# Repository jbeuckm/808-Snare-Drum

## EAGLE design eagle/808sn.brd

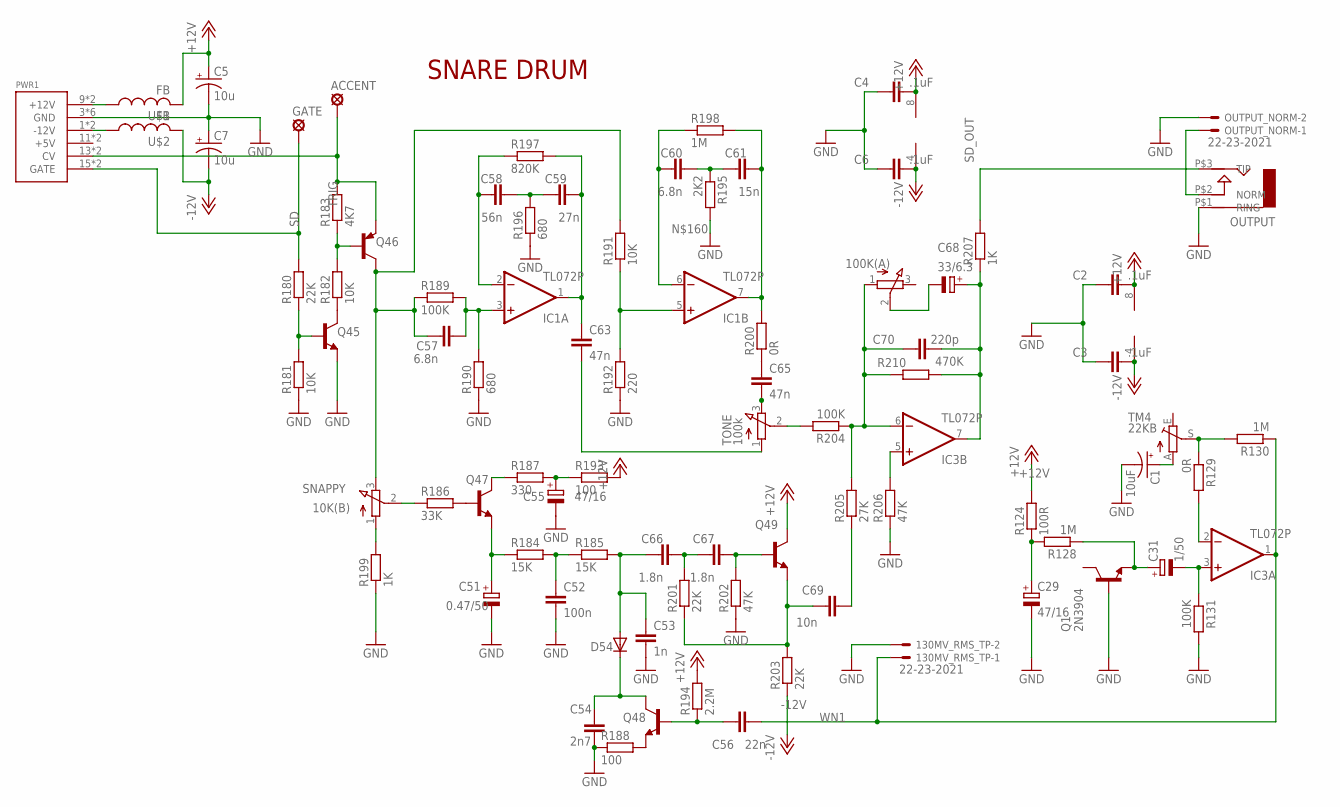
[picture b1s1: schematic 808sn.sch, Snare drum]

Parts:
130MV_RMS_TP: 22-23-2021
ACCENT: LSP10
C1: 10uF; B45181A
C2, C3, C4: .1uF; C025-025X050
C5, C7: 10u; B45181A
C6: .1uF; C050-025X075
C29: 47/16; E2,5-5
C31: 1/50; E3,5-8
C51: 0.47/50; E3,5-8
C52: 100n; C050-045X075
C53: 1n; C035-025X75
C54: 2n7; C035-025X75
C55: 47/16; E2-5
C56: 22n; C035-030X60
C57, C60: 6.8n; C035-030X60
C58: 56n; C050-024X044
C59: 27n; C050-024X044
C61: 15n; C035-030X60
C63, C65: 47n; C050-024X044
C66, C67: 1.8n; C035-025X75
C68: 33/6.3; E2-5
C69: 10n; C075-042X103
C70: 220p; C025-025X050
D54: 1N4148DO35-7; DO35-7
GATE: LSP10
IC1, IC3: TL072P; DIL08
LEVEL: 100K(A); 3RP/1610N
OUTPUT: AUDIO-JACK; ERTHENVAR-JACK-90DEG
OUTPUT_NORM: 22-23-2021
PWR1: POWER; POWER_16
Q1, Q45, Q47, Q48, Q49: 2N3904; TO92
Q46: 2N3906; TO92
R124: 100R; 0207/7
R128, R130: 1M; 0207/7
R129: 0R; 0207/7
R131, R204: 100K; 0207/7
R180: 22K; 0207/5V
R181, R182, R191: 10K; 0207/5V
R183: 4K7; 0207/2V
R184, R185: 15K; 0207/7
R186: 33K; 0309/12
R187: 330; 0207/7
R188: 100; 0207/5V
R189: 100K; 0207/5V
R190: 680; 0207/5V
R192: 220; 0207/5V
R193: 100; 0207/7
R194: 2.2M; 0207/7
R195: 2K2; 0207/7
R196: 680; 0207/7
R197: 820K; 0207/5V
R198: 1M; 0207/5V
R199: 1K; 0207/5V
R200: 0R; 0207/5V
R201, R203: 22K; 0207/7
R202, R206: 47K; 0207/5V
R205: 27K; 0207/7
R207: 1K; 0309/10
R210: 470K; 0207/5V
SNAPPY: 10K(B); 3RP/1610N
TM4: 22KB; B64Y
TONE: 100k; 3RP/1610N
U$1, U$2: FB

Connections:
+12V: C2.2, C4.2, C5.+, IC1.8 (V+), IC3.8 (V+), Q49.1 (C), R124.2, R193.2, R194.2, U$1.P$2 (2)
-12V: C3.2, C6.2, C7.-, IC1.4 (V-), IC3.4 (V-), R203.1, U$2.P$2 (2)
GND: 130MV_RMS_TP.2, C1.-, C2.1, C3.1, C4.1, C5.-, C6.1, C7.+, C29.-, C51.-, C52.2, C53.P$2 (2), C54.P$2 (2), C55.-, OUTPUT.P$1 (RING), OUTPUT_NORM.2, PWR1.3 (GND), PWR1.4 (GND), PWR1.5 (GND), PWR1.6 (GND), PWR1.7 (GND), PWR1.8 (GND), Q1.2 (B), Q45.3 (E), R131.2, R181.1, R188.1, R190.1, R192.1, R195.2, R196.1, R199.1, R202.1, R206.1
unnamed: IC3.5 (+IN), R206.2
unnamed: OUTPUT.P$2 (NORM), OUTPUT_NORM.1
unnamed: C1.+, TM4.A
unnamed: IC3.2 (-IN), R129.2
unnamed: Q45.2 (B), R180.1, R181.2
unnamed: Q46.2 (B), R182.2, R183.1
unnamed: Q45.1 (C), R182.1
unnamed: C57.P$2 (2), IC1.3 (+IN), R189.2, R190.2
unnamed: C57.P$1 (1), Q46.1 (C), R189.1, R191.2, SNAPPY.3 (E)
unnamed: PWR1.9 (+12V), PWR1.10 (+12V), U$1.P$1 (1)
unnamed: C58.1, IC1.2 (-IN), R197.1
unnamed: C59.2, C63.1, IC1.1 (OUT), R197.2
unnamed: C58.2, C59.1, R196.2
unnamed: C61.P$2 (2), IC1.7 (OUT), R198.2, R200.2
unnamed: C60.P$2 (2), C61.P$1 (1), R195.1
unnamed: IC1.5 (+IN), R191.1, R192.2
unnamed: C63.2, TONE.1 (A)
unnamed: C65.2, TONE.3 (E)
unnamed: C65.1, R200.1
unnamed: R199.2, SNAPPY.1 (A)
unnamed: C52.1, R184.2, R185.1
unnamed: R186.1, SNAPPY.2 (S)
unnamed: Q47.2 (B), R186.2
unnamed: Q47.1 (C), R187.1
unnamed: C55.+, R187.2, R193.1
unnamed: C51.+, Q47.3 (E), R184.1
unnamed: C53.P$1 (1), C66.P$1 (1), D54.A, R185.2
unnamed: C66.P$2 (2), C67.P$1 (1), R201.2
unnamed: C67.P$2 (2), Q49.2 (B), R202.2
unnamed: C69.1, Q49.3 (E), R201.1, R203.2
unnamed: Q48.3 (E), R188.2
unnamed: C54.P$1 (1), D54.C, Q48.1 (C)
unnamed: C56.P$1 (1), Q48.2 (B), R194.1
unnamed: R204.2, TONE.2 (S)
unnamed: C70.1, IC3.6 (-IN), LEVEL.1 (A), R204.1, R205.2, R210.1
unnamed: C69.2, R205.1
unnamed: PWR1.1 (-12V), PWR1.2 (-12V), U$2.P$1 (1)
unnamed: C68.+, C70.2, IC3.7 (OUT), R207.1, R210.2
unnamed: C68.-, LEVEL.2 (S)
unnamed: C60.P$1 (1), IC1.6 (-IN), R198.1
unnamed: C31.-, IC3.3 (+IN), R131.1
unnamed: R129.1, R130.2, TM4.S
unnamed: C31.+, Q1.3 (E), R128.1
unnamed: C29.+, R124.1, R128.2
SD: GATE.MP, PWR1.15 (GATE), PWR1.16 (GATE), R180.2
SD_OUT: OUTPUT.P$3 (TIP), R207.2
TRIG: ACCENT.MP, PWR1.13 (CV), PWR1.14 (CV), Q46.3 (E), R183.2
WN1: 130MV_RMS_TP.1, C56.P$2 (2), IC3.1 (OUT), R130.1

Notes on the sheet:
SNARE DRUM

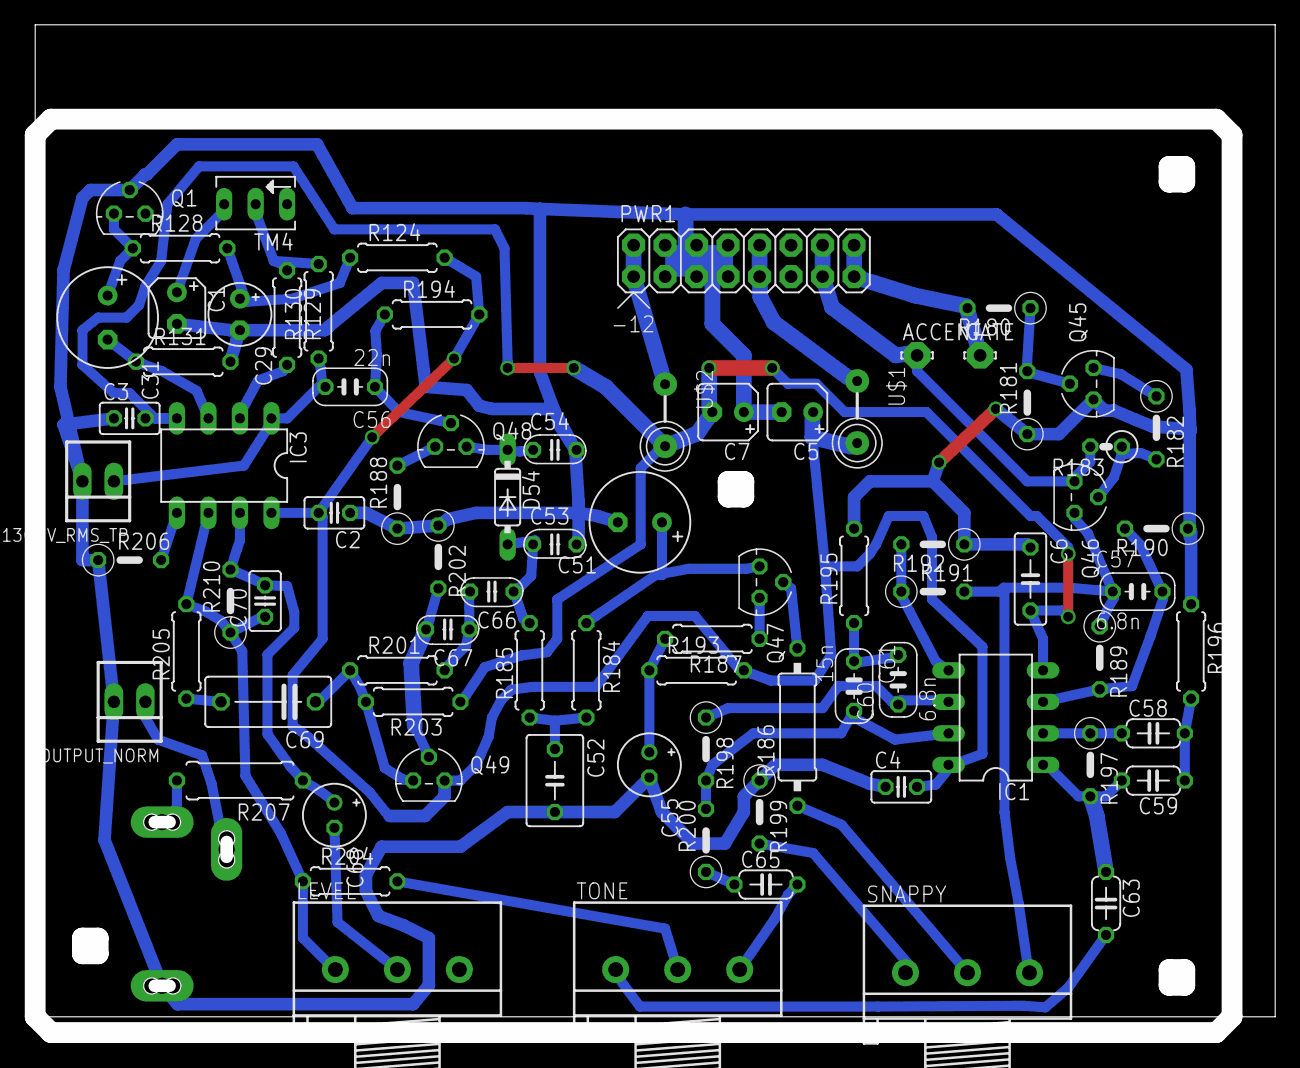
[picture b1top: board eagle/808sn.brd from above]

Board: 2 copper layers, 99.2 x 80.4 mm, 82 parts (0 on the bottom side), 51 nets.

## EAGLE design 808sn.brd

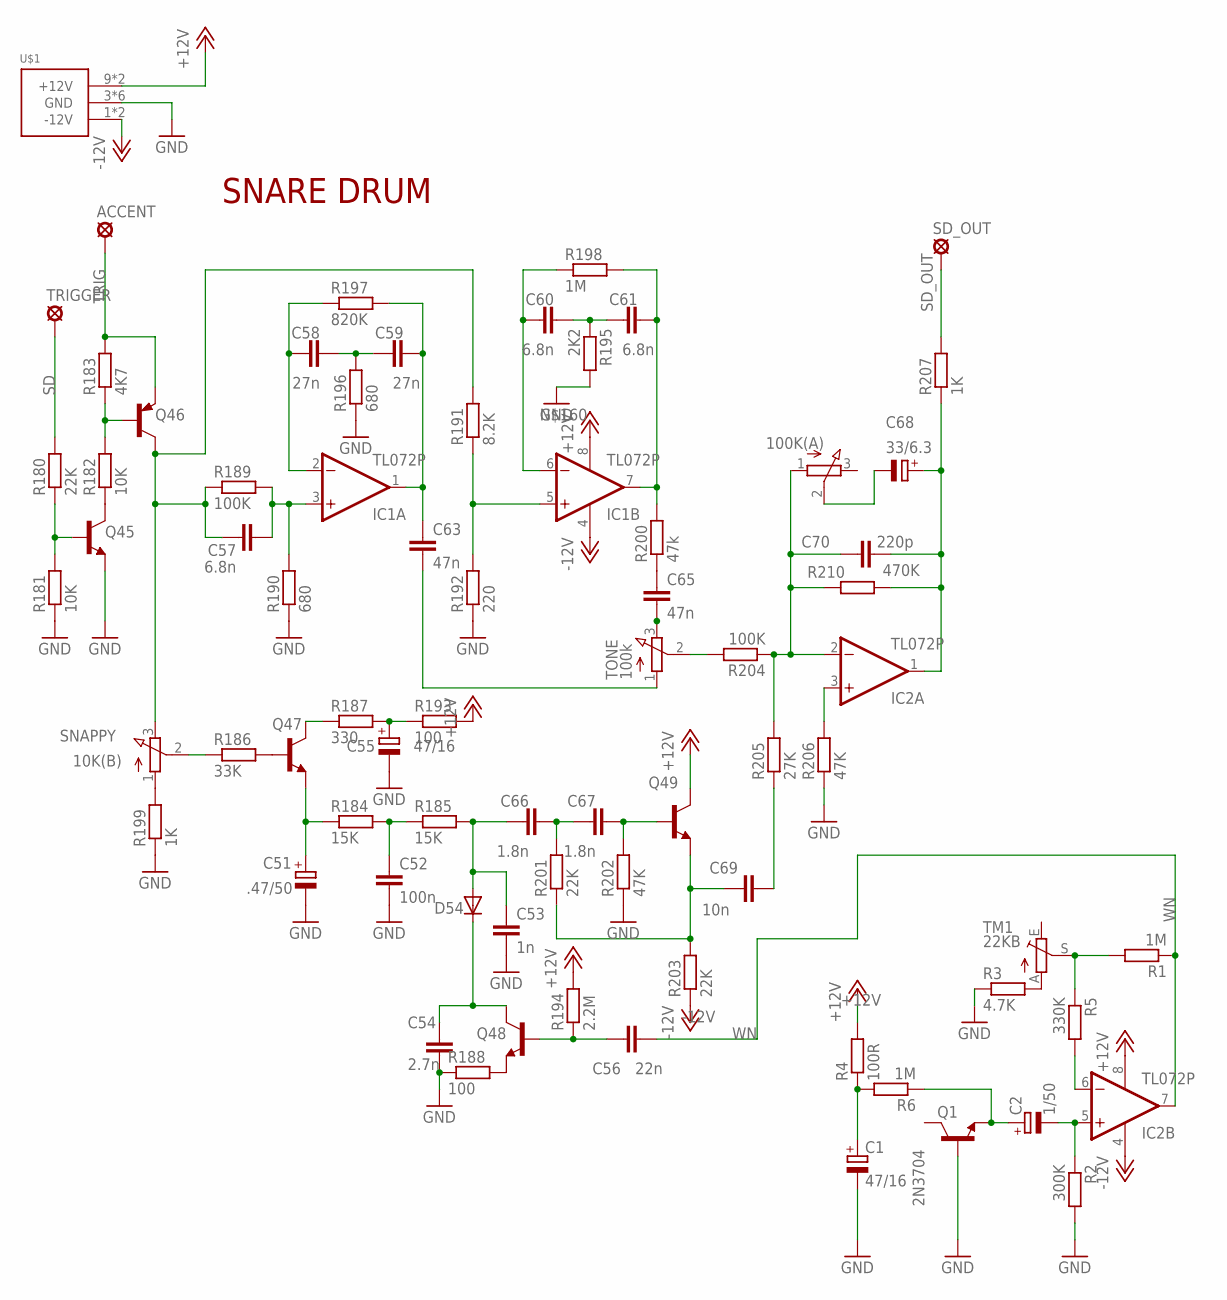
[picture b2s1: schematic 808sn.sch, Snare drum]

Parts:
ACCENT: LSP11
C1: 47/16; E2,5-5
C2: 1/50; E2,5-5
C51: .47/50; E2-5
C52: 100n; C075-032X103
C53: 1n; C035-025X75
C54: 2.7n; C035-025X75
C55: 47/16; E2-5
C56: 22n; C035-030X60
C57, C60, C61: 6.8n; C035-030X60
C58, C59: 27n; C050-024X044
C63, C65: 47n; C050-024X044
C66, C67: 1.8n; C035-025X75
C68: 33/6.3; E2-5
C69: 10n; C035-025X75
C70: 220p; C025-025X050
D54: 1N4148DO35-7; DO35-7
IC1, IC2: TL072P; DIL08
LEVEL: 100K(A); 3RP/1610N
Q1: 2N3704; TO92
Q45, Q47, Q48, Q49: BC546A; TO92-EBC
Q46: BC556; TO92-EBC
R1, R6, R198: 1M; 0207/5V
R2: 300K; 0207/5V
R3: 4.7K; 0207/5V
R4: 100R; 0207/5V
R5: 330K; 0207/5V
R180, R201, R203: 22K; 0207/5V
R181, R182: 10K; 0207/5V
R183: 4K7; 0207/5V
R184, R185: 15K; 0207/5V
R186: 33K; 0207/5V
R187: 330; 0207/5V
R188, R193: 100; 0207/5V
R189, R204: 100K; 0207/5V
R190, R196: 680; 0207/5V
R191: 8.2K; 0207/5V
R192: 220; 0207/5V
R194: 2.2M; 0207/5V
R195: 2K2; 0207/5V
R197: 820K; 0207/5V
R199, R207: 1K; 0207/5V
R200: 47k; 0207/5V
R202, R206: 47K; 0207/5V
R205: 27K; 0207/5V
R210: 470K; 0207/5V
SD_OUT: LSP11
SNAPPY: 10K(B); 3RP/1610N
TM1: 22KB; S64YW
TONE: 100k; 3RP/1610N
TRIGGER: LSP11
U$1: POWER_SIMPLE10; POWER_10

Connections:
+12V: IC1.8 (V+), IC2.8 (V+), Q49.C, R4.2, R193.2, R194.2, U$1.9 (+12V), U$1.10 (+12V)
-12V: IC1.4 (V-), IC2.4 (V-), R203.1, U$1.1 (-12V), U$1.2 (-12V)
GND: C1.-, C51.-, C52.2, C53.P$2 (2), C54.P$2 (2), C55.-, Q1.1 (B), Q45.E, R2.2, R3.1, R181.1, R188.1, R190.1, R192.1, R195.2, R196.1, R199.1, R202.1, R206.1, U$1.3 (GND), U$1.4 (GND), U$1.5 (GND), U$1.6 (GND), U$1.7 (GND), U$1.8 (GND)
unnamed: IC2.3 (+IN), R206.2
unnamed: C2.-, IC2.5 (+IN), R2.1
unnamed: IC2.6 (-IN), R5.2
unnamed: Q45.B, R180.1, R181.2
unnamed: Q46.B, R182.2, R183.1
unnamed: Q45.C, R182.1
unnamed: C57.P$2 (2), IC1.3 (+IN), R189.2, R190.2
unnamed: C57.P$1 (1), Q46.C, R189.1, R191.2, SNAPPY.3 (E)
unnamed: C58.1, IC1.2 (-IN), R197.1
unnamed: C59.2, C63.1, IC1.1 (OUT), R197.2
unnamed: C58.2, C59.1, R196.2
unnamed: C61.P$2 (2), IC1.7 (OUT), R198.2, R200.2
unnamed: C60.P$2 (2), C61.P$1 (1), R195.1
unnamed: IC1.5 (+IN), R191.1, R192.2
unnamed: C63.2, TONE.1 (A)
unnamed: C65.2, TONE.3 (E)
unnamed: C65.1, R200.1
unnamed: R199.2, SNAPPY.1 (A)
unnamed: C52.1, R184.2, R185.1
unnamed: R186.1, SNAPPY.2 (S)
unnamed: Q47.B, R186.2
unnamed: Q47.C, R187.1
unnamed: C55.+, R187.2, R193.1
unnamed: C51.+, Q47.E, R184.1
unnamed: C53.P$1 (1), C66.P$1 (1), D54.A, R185.2
unnamed: C66.P$2 (2), C67.P$1 (1), R201.2
unnamed: C67.P$2 (2), Q49.B, R202.2
unnamed: C69.P$1 (1), Q49.E, R201.1, R203.2
unnamed: Q48.E, R188.2
unnamed: C54.P$1 (1), D54.C, Q48.C
unnamed: C56.P$1 (1), Q48.B, R194.1
unnamed: R204.2, TONE.2 (S)
unnamed: C70.1, IC2.2 (-IN), LEVEL.1 (A), R204.1, R205.2, R210.1
unnamed: C69.P$2 (2), R205.1
unnamed: C68.+, C70.2, IC2.1 (OUT), R207.1, R210.2
unnamed: C68.-, LEVEL.2 (S)
unnamed: C60.P$1 (1), IC1.6 (-IN), R198.1
unnamed: R1.2, R5.1, TM1.S
unnamed: C2.+, Q1.3 (E), R6.1
unnamed: C1.+, R4.1, R6.2
unnamed: R3.2, TM1.A
SD: R180.2, TRIGGER.MP
SD_OUT: R207.2, SD_OUT.MP
TRIG: ACCENT.MP, Q46.E, R183.2
WN: C56.P$2 (2), IC2.7 (OUT), R1.1

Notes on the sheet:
SNARE DRUM

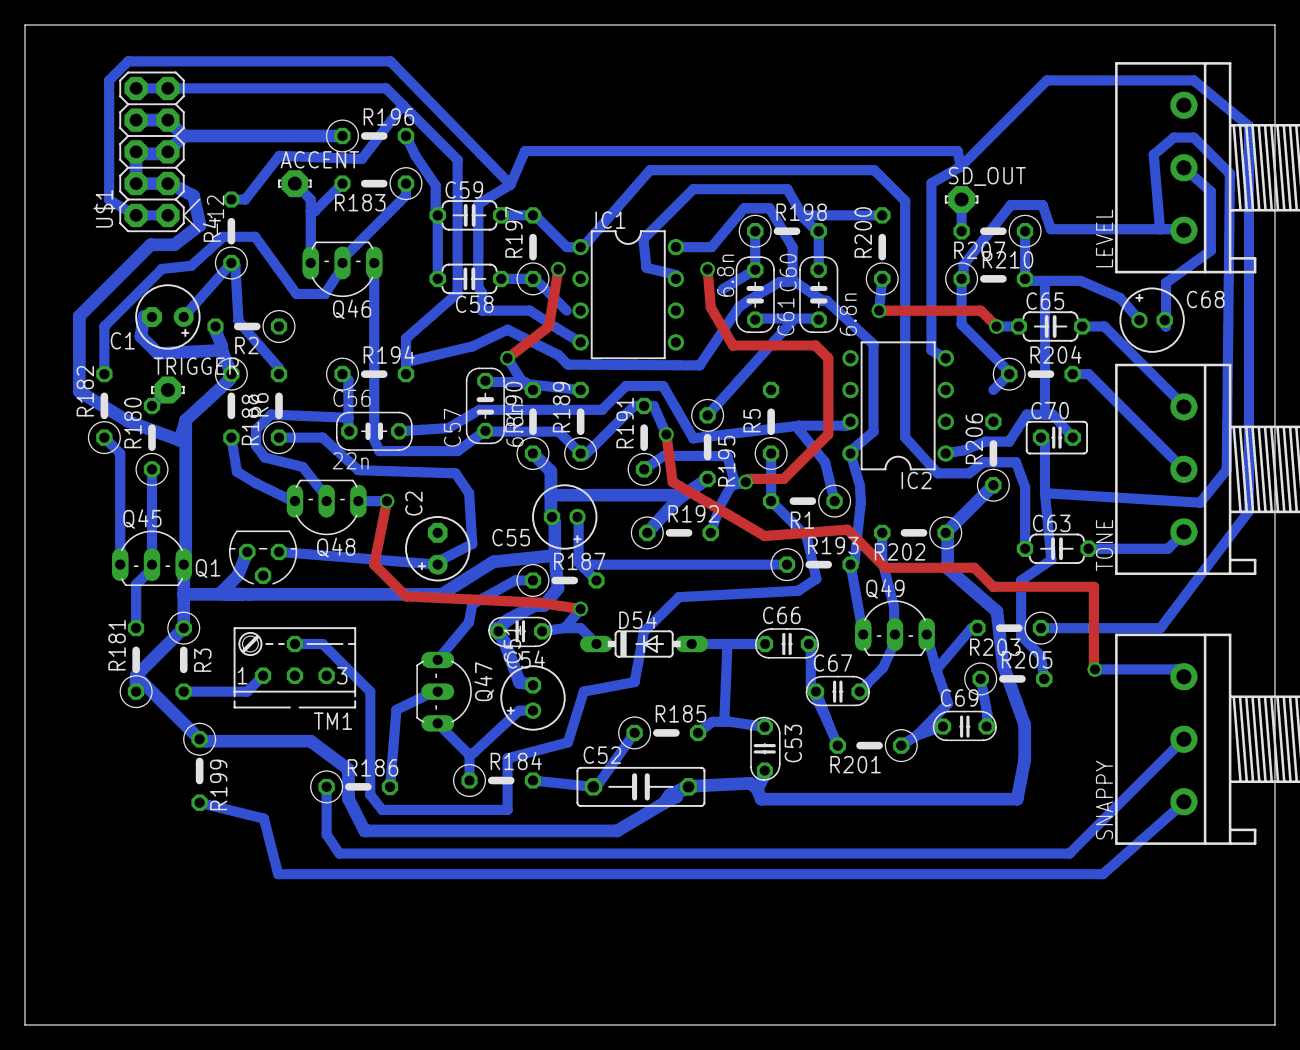
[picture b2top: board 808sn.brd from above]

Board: 2 copper layers, 100.0 x 80.0 mm, 72 parts (0 on the bottom side), 48 nets.

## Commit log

2015-01-11 improved traces to snappy pot
2015-01-17 opamps flipped, working on layout
2015-01-17 decoupling caps and corrected opamp polarities
2015-01-18 almost routed
2015-01-18 gcode with good separation of traces
2016-04-29 updated fittings and replaced with 2n390x
2016-04-29 92pct autorouted
2016-04-30 board started over
2016-04-30 94pct autorouted
2016-04-30 routed
2016-04-30 tweaks
2016-04-30 cutout
2016-05-01 gcode
2016-05-16 svg panel
